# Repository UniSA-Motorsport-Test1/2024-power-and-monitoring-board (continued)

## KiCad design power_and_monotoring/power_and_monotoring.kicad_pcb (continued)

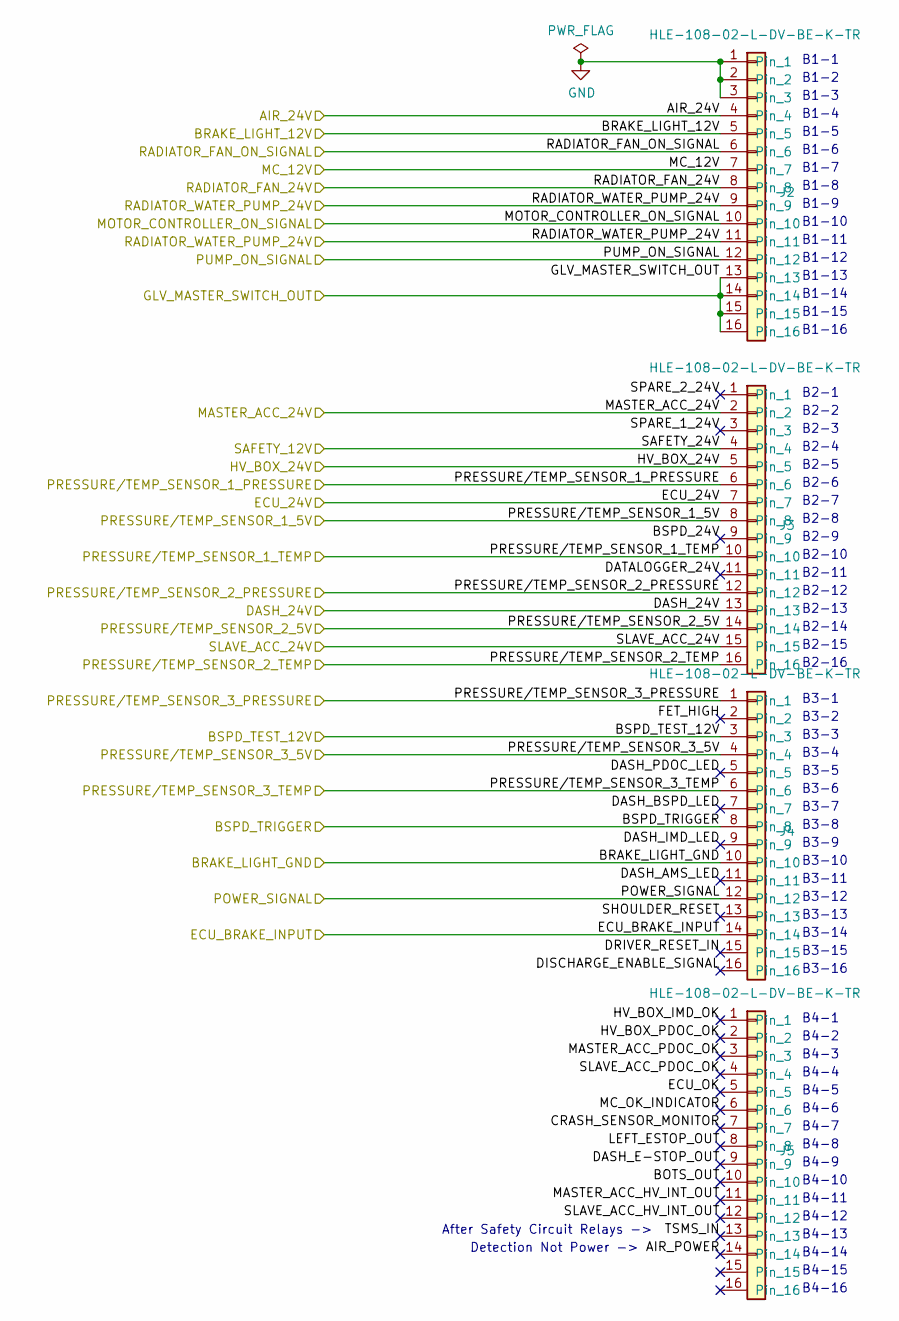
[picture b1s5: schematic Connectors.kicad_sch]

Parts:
J2, J3, J4, J5: HLE-108-02-L-DV-BE-K-TR; SAMTEC_HLE-108-02-L-DV-BE-K-TR

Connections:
+5V: J3.8, J3.14, J4.4; also elsewhere on the board
/Connectors/AIR_24V: J2.4; also elsewhere on the board
/Connectors/AIR_POWER: J5.14
/Connectors/BOTS_OUT: J5.10
/Connectors/BRAKE_LIGHT_12V: J2.5; also elsewhere on the board
/Connectors/BRAKE_LIGHT_GND: J4.10; also elsewhere on the board
/Connectors/BSPD_24V: J3.9
/Connectors/BSPD_TEST_12V: J4.3; also elsewhere on the board
/Connectors/BSPD_TRIGGER: J4.8; also elsewhere on the board
/Connectors/CRASH_SENSOR_MONITOR: J5.7
/Connectors/DASH_24V: J3.13; also elsewhere on the board
/Connectors/DASH_AMS_LED: J4.11
/Connectors/DASH_BSPD_LED: J4.7
/Connectors/DASH_E-STOP_OUT: J5.9
/Connectors/DASH_IMD_LED: J4.9
/Connectors/DASH_PDOC_LED: J4.5
/Connectors/DATALOGGER_24V: J3.11
/Connectors/DISCHARGE_ENABLE_SIGNAL: J4.16
/Connectors/DRIVER_RESET_IN: J4.15
/Connectors/ECU_24V: J3.7; also elsewhere on the board
/Connectors/ECU_BRAKE_INPUT: J4.14; also elsewhere on the board
/Connectors/ECU_OK: J5.5
/Connectors/FET_HIGH: J4.2
/Connectors/GLV_MASTER_SWITCH_OUT: J2.13, J2.14, J2.15, J2.16; also elsewhere on the board
/Connectors/HV_BOX_24V: J3.5; also elsewhere on the board
/Connectors/HV_BOX_IMD_OK: J5.1
/Connectors/HV_BOX_PDOC_OK: J5.2
/Connectors/LEFT_ESTOP_OUT: J5.8
/Connectors/MASTER_ACC_24V: J3.2; also elsewhere on the board
/Connectors/MASTER_ACC_HV_INT_OUT: J5.11
/Connectors/MASTER_ACC_PDOC_OK: J5.3
/Connectors/MC_12V: J2.7; also elsewhere on the board
/Connectors/MC_OK_INDICATOR: J5.6
/Connectors/MOTOR_CONTROLLER_ON_SIGNAL: J2.10; also elsewhere on the board
/Connectors/POWER_SIGNAL: J4.12; also elsewhere on the board
/Connectors/PRESSURE/TEMP_SENSOR_1_PRESSURE: J3.6; also elsewhere on the board
/Connectors/PRESSURE/TEMP_SENSOR_1_TEMP: J3.10; also elsewhere on the board
/Connectors/PRESSURE/TEMP_SENSOR_2_PRESSURE: J3.12; also elsewhere on the board
/Connectors/PRESSURE/TEMP_SENSOR_2_TEMP: J3.16; also elsewhere on the board
/Connectors/PRESSURE/TEMP_SENSOR_3_PRESSURE: J4.1; also elsewhere on the board
/Connectors/PRESSURE/TEMP_SENSOR_3_TEMP: J4.6; also elsewhere on the board
/Connectors/PUMP_ON_SIGNAL: J2.12; also elsewhere on the board
/Connectors/RADIATOR_FAN_24V: J2.8; also elsewhere on the board
/Connectors/RADIATOR_FAN_ON_SIGNAL: J2.6; also elsewhere on the board
/Connectors/RADIATOR_WATER_PUMP_24V: J2.9, J2.11; also elsewhere on the board
/Connectors/SAFETY_24V: J3.4; also elsewhere on the board
/Connectors/SHOULDER_RESET: J4.13
/Connectors/SLAVE_ACC_24V: J3.15; also elsewhere on the board
/Connectors/SLAVE_ACC_HV_INT_OUT: J5.12
/Connectors/SLAVE_ACC_PDOC_OK: J5.4
/Connectors/SPARE_1_24V: J3.3
/Connectors/SPARE_2_24V: J3.1
/Connectors/TSMS_IN: J5.13
GND: J2.1, J2.2, J2.3; also elsewhere on the board

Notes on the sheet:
B4-14
B3-5
B2-14
B2-9
B2-2
B3-8
B3-9
B3-11
B3-15
B2-15
B2-4
B4-3
B3-4
B2-16
B4-7
After Safety Circuit Relays ->
B1-9
B2-8
B4-5
B1-4
B1-2
B4-9
Detection Not Power ->
B3-12
B1-12
B2-6
B1-6
B4-10
B1-14
B1-8
B3-2
B4-1
B3-10
B3-1
B2-13
B1-7
B4-2
B2-3
B4-12
B3-13

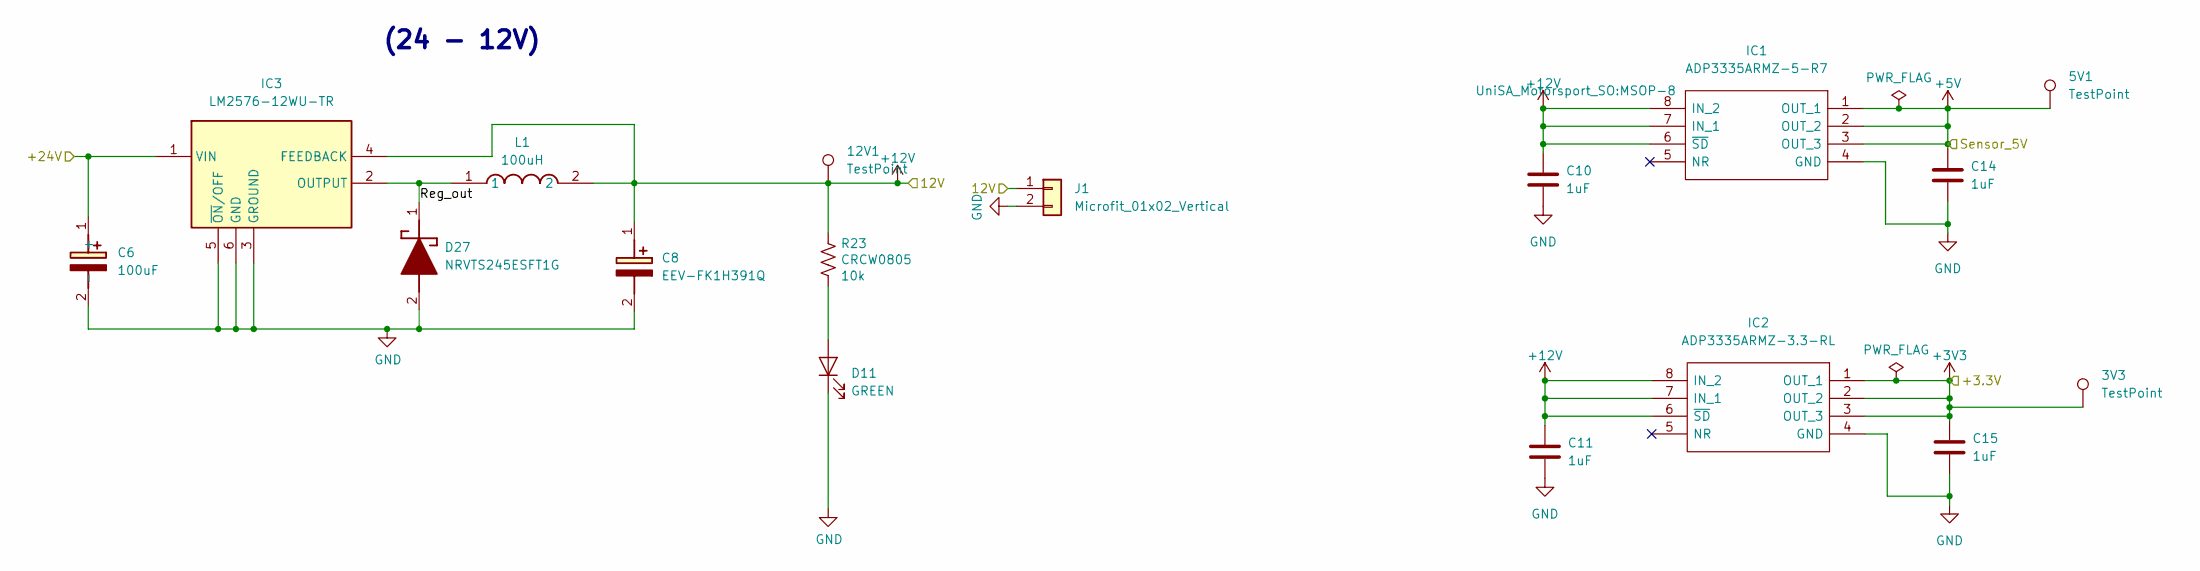
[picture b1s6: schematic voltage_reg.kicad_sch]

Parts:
3V3, 5V1, 12V1: TestPoint; TestPoint_Pad_D2.0mm
C6: 100uF; EEEFK0J332AQ
C8: EEV-FK1H391Q; EEEFK0J332AQ; Mouser Part Number 667-EEV-FK1H391Q
C10, C11, C14, C15: 1uF; C_0805_2012Metric
D11: GREEN; 0805
D27: NRVTS245ESFT1G; SOD-123FL-2; Mouser Part Number 863-NRVTS245ESFT1G
IC1: ADP3335ARMZ-5-R7; MSOP-8; Mouser Part Number 584-ADP3335ARMZ-5-R7
IC2: ADP3335ARMZ-3.3-RL; MSOP-8; Mouser Part Number 584-ADP3335ARMZ3.3R
IC3: LM2576-12WU-TR; TO-263-5; Mouser Part Number 998-LM2576-12WUTR
J1: Microfit_01x02_Vertical; Molex_Micro-Fit_43650-0215_1x02_Vertical
L1: 100uH; 5050
R23: CRCW0805; 0805; Voltage Rating 50V; Power Rating 63mW

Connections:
+3V3: 3V3.1, C15.1, IC2.1 (OUT_1), IC2.2 (OUT_2), IC2.3 (OUT_3); also elsewhere on the board
+5V: 5V1.1, C14.1, IC1.1 (OUT_1), IC1.2 (OUT_2), IC1.3 (OUT_3); also elsewhere on the board
+12V: 12V1.1, C8.1 (+), C10.1, C11.1, IC1.6 (~SD), IC1.7 (IN_1), IC1.8 (IN_2), IC2.6 (~SD), IC2.7 (IN_1), IC2.8 (IN_2), IC3.4 (FEEDBACK), J1.1, L1.2, R23.1; also elsewhere on the board
+24V: C6.1 (+), IC3.1 (VIN); also elsewhere on the board
/voltage_reg/Reg_out: D27.1 (K), IC3.2 (OUTPUT), L1.1
GND: C6.2 (-), C8.2 (-), C10.2, C11.2, C14.2, C15.2, D11.1 (K), D27.2 (A), IC1.4 (GND), IC2.4 (GND), IC3.3 (GROUND), IC3.5 (~ON/OFF), IC3.6 (GND), J1.2; also elsewhere on the board
unnamed: D11.2 (A), R23.2

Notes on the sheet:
(24 - 12V)

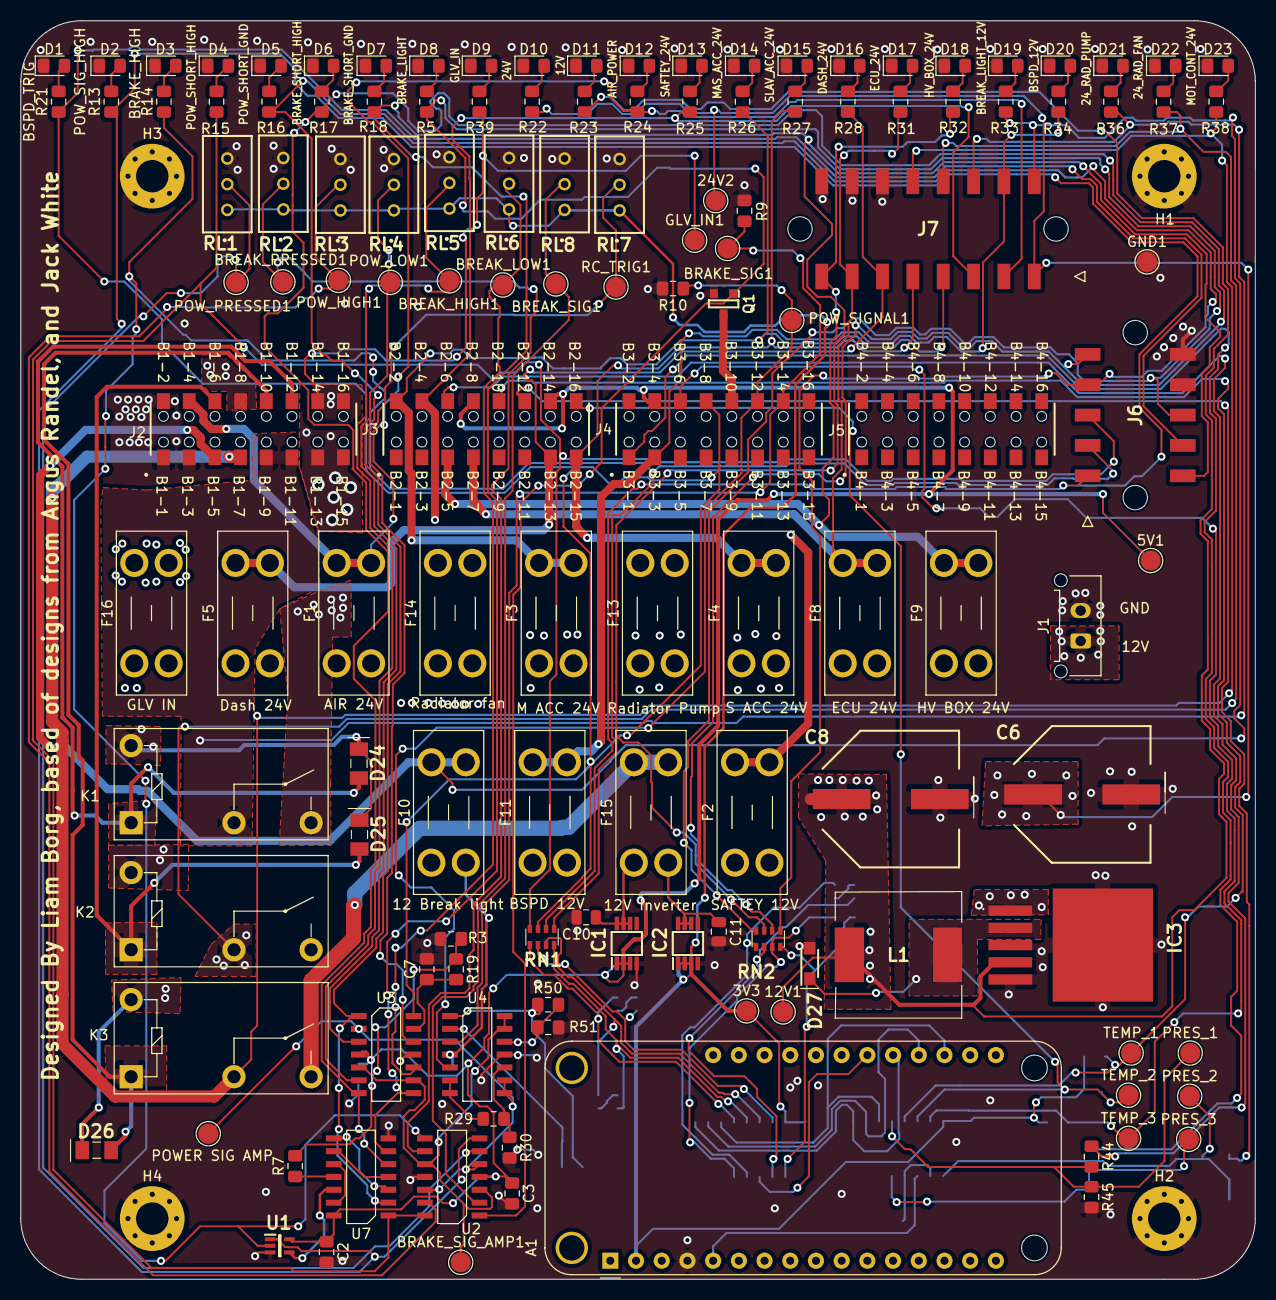
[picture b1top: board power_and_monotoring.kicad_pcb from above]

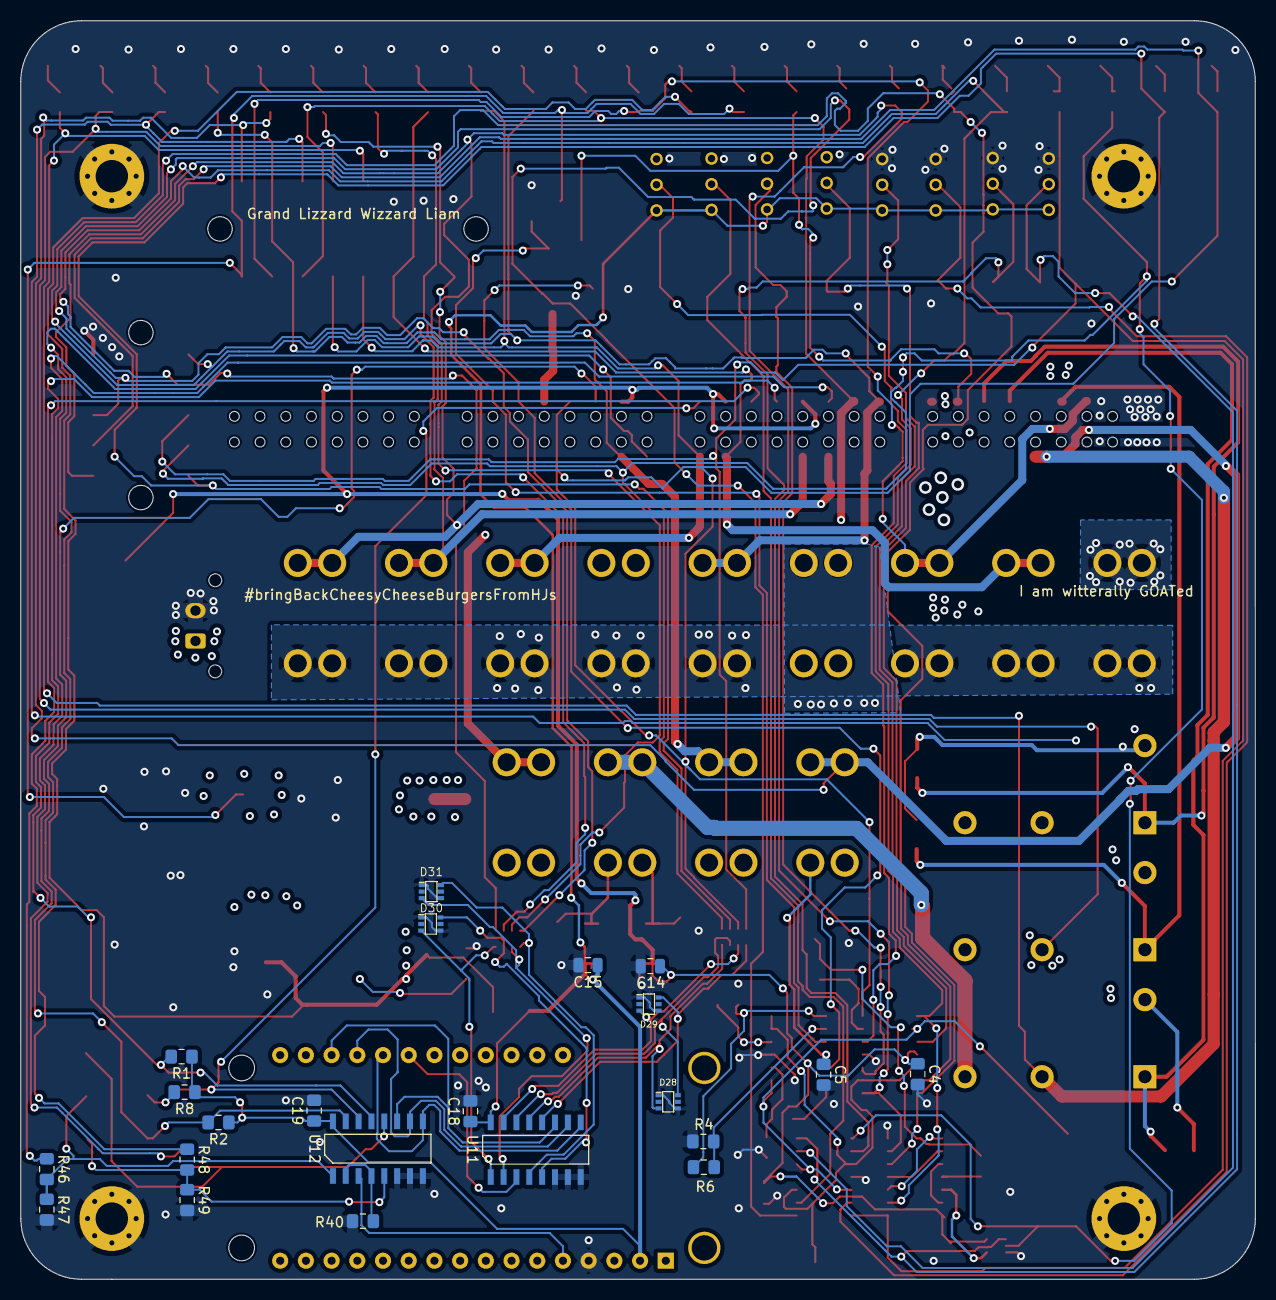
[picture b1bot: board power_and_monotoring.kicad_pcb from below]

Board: 4 copper layers, 122.0 x 124.4 mm, 162 parts (22 on the bottom side), 104 nets.

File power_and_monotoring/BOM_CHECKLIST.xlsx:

Reference | Value | Datasheet | Footprint | Qty | DNP
3V3,5V1,12V1,24V2,BRAKE_SIG1,BRAKE_SIG_AMP1,BREAK_HIGH1,BREAK_LOW1,BREAK_PRESSE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 | TestPoint | ~ | TestPoint:TestPoint_Pad_D2.0mm | 24
A1 | Adafruit_Feather_Generic | https://cdn-learn.adafruit.com/downloads/pdf/adafruit-feather.pdf | Module:Adafruit_Feather_WithMountingHoles | 1
C2,C3,C4,C5 | GCM0805_1u | https://au.mouser.com/datasheet/2/281/murata_03122018_GCM_Se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 | UniSA_Motorsport_Capacitor:0805 | 4
C6 | 100uF | https://au.mouser.com/ProductDetail/Panasonic/EEE-FK1H101P?q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 | UniSA_Motorsport_Capacitor:EEEFK0J332AQ | 1
C7 | GCM0805_2.2u | https://au.mouser.com/datasheet/2/281/murata_03122018_GCM_Se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 | UniSA_Motorsport_Capacitor:0805 | 1
C8 | EEV-FK1H391Q | https://au.mouser.com/ProductDetail/Panasonic/EEV-FK1H391Q?q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 | UniSA_Motorsport_Capacitor:EEEFK0J332AQ | 1
C10,C11,C14,C15 | 1uF | ~ | Capacitor_SMD:C_0805_2012Metric | 4
C18,C19 | GCM0805_0.1u | https://au.mouser.com/datasheet/2/281/murata_03122018_GCM_Se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 | UniSA_Motorsport_Capacitor:0805 | 2
D1,D2,D3,D4,D5,D6,D7 | RED | https://au.mouser.com/datasheet/2/109/Dialight_CBI_data_599-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 | UniSA_Motorsport_Diode:0805 | 7
D8,D9,D10,D11,D12,D13,D14,D15,D16,D17,D18,D19,D20,D21,D22,D23 | GREEN | https://au.mouser.com/datasheet/2/109/Dialight_CBI_data_599-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 | UniSA_Motorsport_Diode:0805 | 16
D24,D25,D26 | 1N4148W RHG | https://au.mouser.com/ProductDetail/Taiwan-Semiconductor/1N4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 | UniSA_Motorsport_Diode:SOD-123F-2 | 3
D27 | NRVTS245ESFT1G | https://www.onsemi.com/pub/Collateral/NRVTS245ESF-D.PDF | UniSA_Motorsport_Diode:SOD-123FL-2 | 1
D28,D29,D30,D31 | MMBZ5225BS-7-F | https://au.mouser.com/ProductDetail/Diodes-Incorporated/MMBZ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 | UniSA_Motorsport_SOT_TO:SOT-363 | 4
F1,F2,F3,F4,F5,F8,F9,F10,F11,F13,F14,F15,F16 | Micro Auto Fuse 3568 | https://au.mouser.com/datasheet/2/240/Littelfuse_Fuse_154_15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 | Fuse:Fuseholder_Blade_Mini_Keystone_3568 | 13
H1,H2,H3,H4 | MountingHole_Pad | ~ | MountingHole:MountingHole_3.2mm_M3_Pad_Via | 4
IC1 | ADP3335ARMZ-5-R7 | http://www.analog.com/static/imported-files/data_sheets/ADP3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 | UniSA_Motorsport_SO:MSOP-8 | 1
IC2 | ADP3335ARMZ-3.3-RL | https://www.analog.com/media/en/technical-documentation/data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 | UniSA_Motorsport_SO:MSOP-8 | 1
IC3 | LM2576-12WU-TR | https://www.microchip.com/content/dam/mchp/documents/APID/Pr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 | UniSA_Motorsport_SO:TO-263-5 | 1
J1 | Microfit_01x02_Vertical | ~ | UniSA_Motorsport_Connector:Molex_Micro-Fit_43650-0215_1x02_Vertical | 1
J2,J3,J4,J5 | HLE-108-02-L-DV-BE-K-TR | https://au.mouser.com/ProductDetail/Samtec/HLE-108-02-L-DV-B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 | UniSA_Motorsport_Connector:SAMTEC_HLE-108-02-L-DV-BE-K-TR | 4
J6 | 43045-1015 | https://au.mouser.com/ProductDetail/Molex/43045-1015?qs=g5f4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 | UniSA_Motorsport_Connector:MOLEX_43045-10YY_10PIN | 1
J7 | 43045-1615 | https://au.mouser.com/ProductDetail/Molex/43045-1615?qs=pWIR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 | UniSA_Motorsport_Connector:MOLEX_43045-16YY_16PIN | 1
K1,K2,K3 | G5Q-1A | https://www.omron.com/ecb/products/pdf/en-g5q.pdf | Relay_THT:Relay_SPST_Omron-G5Q-1A | 3
L1 | 100uH | https://au.mouser.com/ProductDetail/Bourns/SRR1260-101M?qs=u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 | UniSA_Motorsport_Inductor:5050 | 1
Q1 | DMN6075SQ-7 | https://www.diodes.com/assets/Datasheets/DMN6075SQ.pdf | UniSA_Motorsport_SOT_TO:SOT-23-3 | 1
R1,R2,R3,R4,R5,R6,R7,R8,R9,R10,R13,R14,R15,R16,R17,R18,R19,R21,R22,R23,R24,R25,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 | CRCW0805 | https://au.mouser.com/datasheet/2/427/dcrcwe3-1762152.pdf | UniSA_Motorsport_Resistor:0805 | 44
RL1,RL2,RL3,RL4,RL5,RL6,RL7,RL8 | 10 K | https://au.mouser.com/ProductDetail/Bourns/3296W-1-103LF?qs=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 | UniSA_Motorsport_Resistor:3296W-1 | 8
RN1,RN2 | EXB-38V103JV | https://au.mouser.com/ProductDetail/Panasonic/EXB-38V103JV?q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 | UniSA_Motorsport_Resistor:EXB38V472JV | 2
U1 | 74LVC1G08GW,125 | https://au.mouser.com/datasheet/2/916/74LVC1G08-2937782.pdf | UniSA_Motorsport_SO:TSSOP-5 | 1
U2,U3,U4 | LM7902D | https://www.ti.com/lit/ds/symlink/lm2902.pdf | UniSA_Motorsport_SO:SOIC-14 | 3
U7 | CD4071BM96 | http://www.ti.com/lit/ds/symlink/cd4069ub.pdf?ts=1588337277788 | UniSA_Motorsport_SO:SOIC-14 | 1
U11,U12 | CD4051BM96G3 | http://www.ti.com/lit/ds/symlink/cd4051b.pdf?ts=1588338734665 | UniSA_Motorsport_SO:SOIC-16 | 2

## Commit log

2024-03-10 Finished shematic and initial layout (NO CONNECTIONS))
2024-03-19 first connections done (not perfect yet)
2024-04-23 before design review
2024-07-14 Final
2024-09-12 Updated 12 Sep
2024-10-16 Made it 4 layers
2025-01-11 My last update
